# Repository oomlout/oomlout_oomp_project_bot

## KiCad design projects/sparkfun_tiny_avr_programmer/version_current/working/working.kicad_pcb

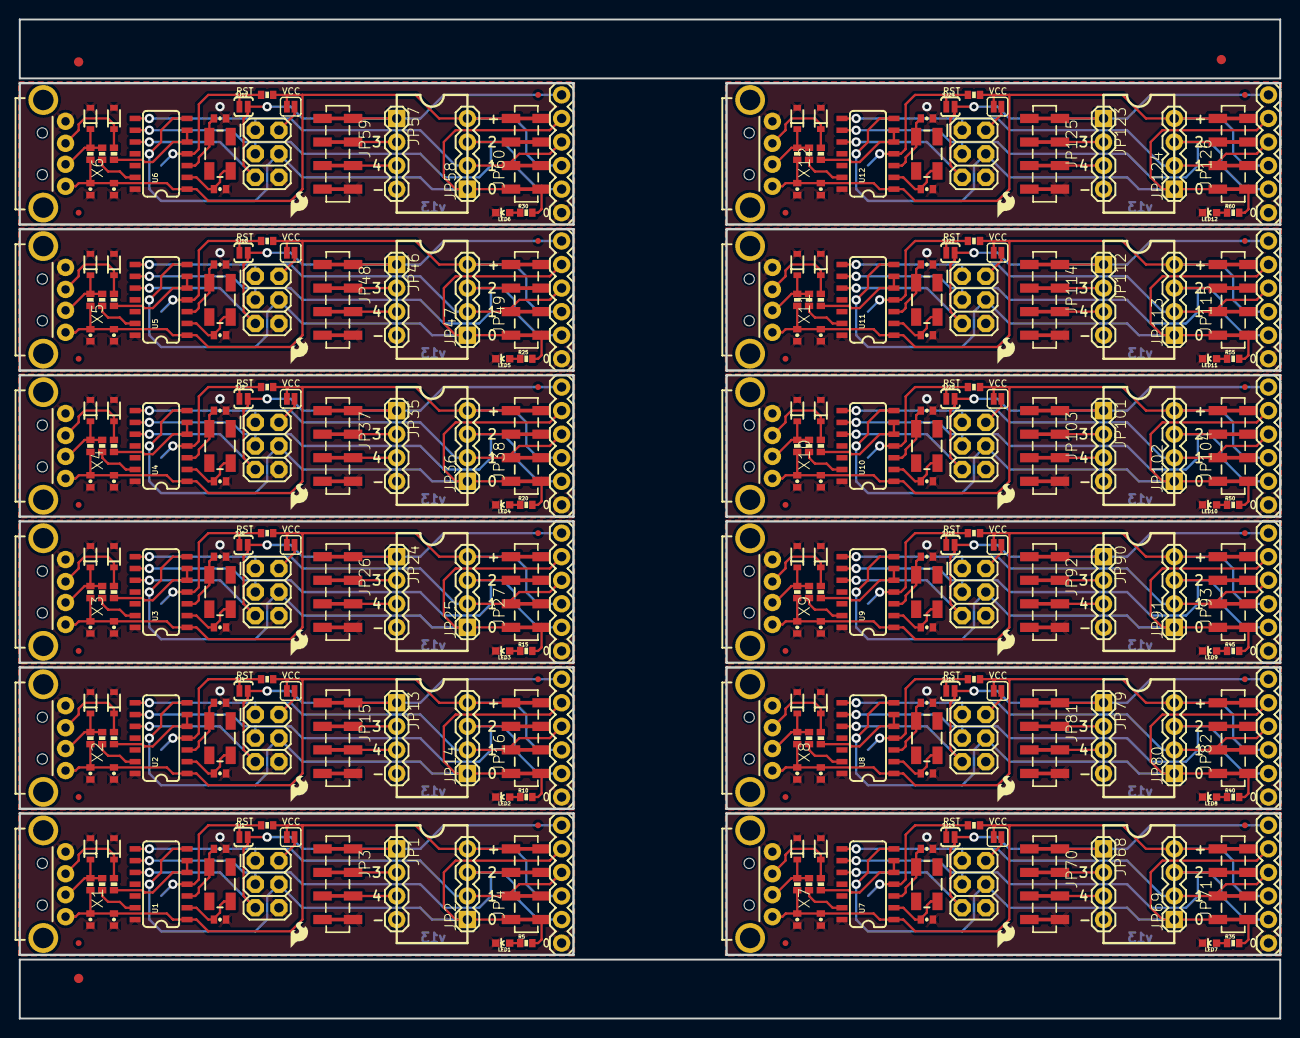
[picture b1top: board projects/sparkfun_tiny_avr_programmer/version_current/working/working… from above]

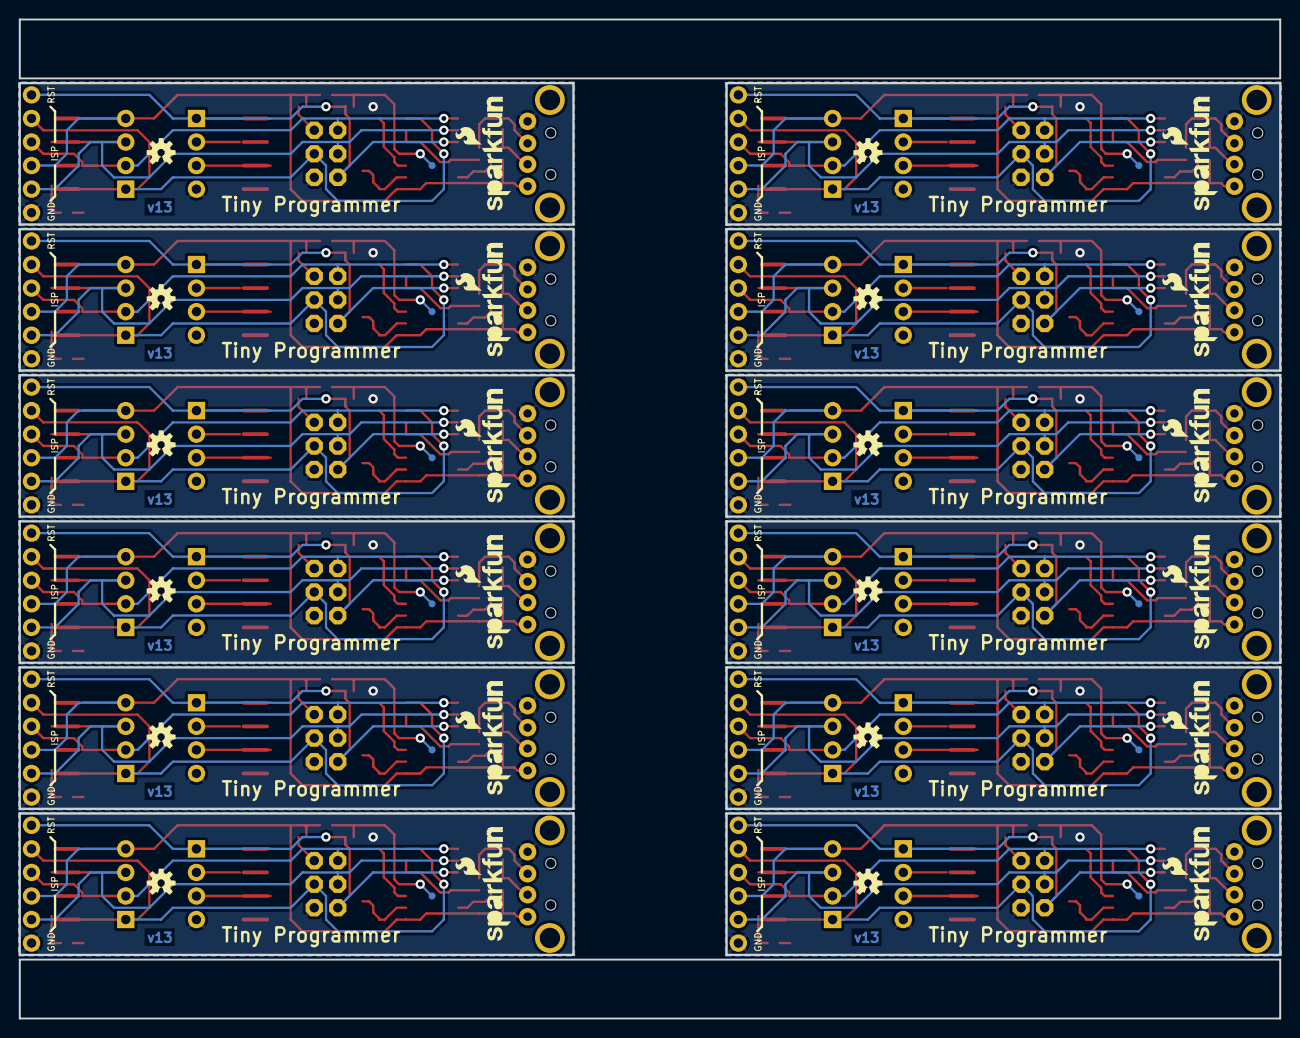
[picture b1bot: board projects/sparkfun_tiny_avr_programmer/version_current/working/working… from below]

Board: 2 copper layers, 135.9 x 107.7 mm, 363 parts (48 on the bottom side), 204 nets.

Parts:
C1, C5, C9, C13, C17, C21, C25, C29, C33, C37, C41, C45: 0.1uF; 0402-CAP
C2, C4, C7, C8, C11, C12, C15, C16, C19, C20, C23, C24, C27, C28, C31, C32, C35, C36, C39, C40, C43, C44, C47, C48: 18pF; 0402-CAP
C3, C6, C10, C14, C18, C22, C26, C30, C34, C38, C42, C46: 10uF; 0402-CAP
D1, D2, D3, D4, D5, D6, D7, D8, D9, D10, D11, D12, D13, D14, D15, D16, D17, D18, D19, D20, D21, D22, D23, D24: 3.3V; SOD-323
E$1, E$3, E$4: FIDUCIAL-1X2
JP1, JP2, JP13, JP14, JP24, JP25, JP35, JP36, JP46, JP47, JP57, JP58, JP68, JP69, JP79, JP80, JP90, JP91, JP101, JP102, JP112, JP113, JP123, JP124: 1X04
JP3, JP4, JP15, JP16, JP26, JP27, JP37, JP38, JP48, JP49, JP59, JP60, JP70, JP71, JP81, JP82, JP92, JP93, JP103, JP104, JP114, JP115, JP125, JP126: 1X04_SMD_STRAIGHT_COMBO
JP5, JP17, JP28, JP39, JP50, JP61, JP72, JP83, JP94, JP105, JP116, JP127: LOGO-SFENW2; SFE-NEW-WEB
JP6, JP11, JP18, JP21, JP29, JP32, JP40, JP43, JP51, JP54, JP62, JP65, JP73, JP76, JP84, JP87, JP95, JP98, JP106, JP109, JP117, JP120, JP128, JP131: LOGO-SFESK; SFE-LOGO-FLAME
JP7, JP8, JP19, JP20, JP30, JP31, JP41, JP42, JP52, JP53, JP63, JP64, JP74, JP75, JP85, JP86, JP96, JP97, JP107, JP108, JP118, JP119, JP129, JP130: FIDUCIALUFIDUCIAL; MICRO-FIDUCIAL
JP9, JP10, JP23, JP34, JP45, JP56, JP67, JP78, JP89, JP100, JP111, JP122: 2X3
JP12, JP22, JP33, JP44, JP55, JP66, JP77, JP88, JP99, JP110, JP121, JP132: 1X06
LED1, LED2, LED3, LED4, LED5, LED6, LED7, LED8, LED9, LED10, LED11, LED12: Yellow; LED-0603
Q1, Q2, Q3, Q4, Q5, Q6, Q7, Q8, Q9, Q10, Q11, Q12: 16MHz; CRYSTAL-SMD-5X3
R1, R2, R6, R7, R11, R12, R16, R17, R21, R22, R26, R27, R31, R32, R36, R37, R41, R42, R46, R47, R51, R52, R56, R57: 68; 0402-RES
R3, R8, R13, R18, R23, R28, R33, R38, R43, R48, R53, R58: 1.5K; 0402-RES
R4, R9, R14, R19, R24, R29, R34, R39, R44, R49, R54, R59: 10k; 0402-RES
R5, R10, R15, R20, R25, R30, R35, R40, R45, R50, R55, R60: 330; 0402-RES
SJ1, SJ4, SJ6, SJ8, SJ10, SJ12, SJ14, SJ16, SJ18, SJ20, SJ22, SJ24: SOLDERJUMPERNO; SJ_2S-NO
SJ2, SJ3, SJ5, SJ7, SJ9, SJ11, SJ13, SJ15, SJ17, SJ19, SJ21, SJ23: NC; SJ_2S
TP1, TP2, TP3, TP4, TP5, TP6, TP7, TP8, TP9, TP10, TP11, TP12: TEST-POINT3; PAD.03X.03
U1, U2, U3, U4, U5, U6, U7, U8, U9, U10, U11, U12: ATTINY84; SO14
U$1, U$2, U$3, U$4, U$5, U$6, U$7, U$8, U$9, U$10, U$11, U$12: OSHW-LOGOS; OSHW-LOGO-S
X1, X2, X3, X4, X5, X6, X7, X8, X9, X10, X11, X12: USB-A-H

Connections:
1: JP13.3, JP15.3
2: JP1.2, JP3.2
3: JP1.3, JP3.3
4: JP13.2, JP15.2
5: JP24.3, JP26.3
6: JP24.2, JP26.2
7: JP35.3, JP37.3
8: JP35.2, JP37.2
9: JP46.3, JP48.3
10: JP46.2, JP48.2
11: JP57.3, JP59.3
12: JP57.2, JP59.2
13: JP68.3, JP70.3
14: JP68.2, JP70.2
15: JP79.3, JP81.3
16: JP79.2, JP81.2
17: JP90.3, JP92.3
18: JP90.2, JP92.2
19: JP101.3, JP103.3
20: JP101.2, JP103.2
21: JP112.3, JP114.3
22: JP112.2, JP114.2
23: JP123.3, JP125.3
24: JP123.2, JP125.2
D+: R2.2, U1.5, U1.6
D+1: R7.2, U2.5, U2.6
D+2: R12.2, U3.5, U3.6
D+3: R17.2, U4.5, U4.6
D+4: R22.2, U5.5, U5.6
D+5: R27.2, U6.5, U6.6
D+6: R32.2, U7.5, U7.6
D+7: R37.2, U8.5, U8.6
D+8: R42.2, U9.5, U9.6
D+9: R47.2, U10.5, U10.6
D+10: R52.2, U11.5, U11.6
D+11: R57.2, U12.5, U12.6
D-: R1.2, U1.13
D-1: R6.2, U2.13
D-2: R11.2, U3.13
D-3: R16.2, U4.13
D-4: R21.2, U5.13
D-5: R26.2, U6.13
D-6: R31.2, U7.13
D-7: R36.2, U8.13
D-8: R41.2, U9.13
D-9: R46.2, U10.13
D-10: R51.2, U11.13
D-11: R56.2, U12.13
GND: C1.2, C2.2, C3.2, C4.2, D1.2, D2.2, JP1.4, JP3.4, JP9.6, JP12.6, LED1.C, U1.14, X1.GND
GND1: C5.2, C6.2, C7.2, C8.2, D3.2, D4.2, JP10.6, JP13.4, JP15.4, JP22.6, LED2.C, U2.14, X2.GND
GND2: C9.2, C10.2, C11.2, C12.2, D5.2, D6.2, JP23.6, JP24.4, JP26.4, JP33.6, LED3.C, U3.14, X3.GND
GND3: C13.2, C14.2, C15.2, C16.2, D7.2, D8.2, JP34.6, JP35.4, JP37.4, JP44.6, LED4.C, U4.14, X4.GND
GND4: C17.2, C18.2, C19.2, C20.2, D9.2, D10.2, JP45.6, JP46.4, JP48.4, JP55.6, LED5.C, U5.14, X5.GND
GND5: C21.2, C22.2, C23.2, C24.2, D11.2, D12.2, JP56.6, JP57.4, JP59.4, JP66.6, LED6.C, U6.14, X6.GND
GND6: C25.2, C26.2, C27.2, C28.2, D13.2, D14.2, JP67.6, JP68.4, JP70.4, JP77.6, LED7.C, U7.14, X7.GND
GND7: C29.2, C30.2, C31.2, C32.2, D15.2, D16.2, JP78.6, JP79.4, JP81.4, JP88.6, LED8.C, U8.14, X8.GND
GND8: C33.2, C34.2, C35.2, C36.2, D17.2, D18.2, JP89.6, JP90.4, JP92.4, JP99.6, LED9.C, U9.14, X9.GND
GND9: C37.2, C38.2, C39.2, C40.2, D19.2, D20.2, JP100.6, JP101.4, JP103.4, JP110.6, LED10.C, U10.14, X10.GND
GND10: C41.2, C42.2, C43.2, C44.2, D21.2, D22.2, JP111.6, JP112.4, JP114.4, JP121.6, LED11.C, U11.14, X11.GND
GND11: C45.2, C46.2, C47.2, C48.2, D23.2, D24.2, JP122.6, JP123.4, JP125.4, JP132.6, LED12.C, U12.14, X12.GND
MISO: JP2.2, JP4.2, JP9.1, JP12.3, U1.8
MISO1: JP10.1, JP14.2, JP16.2, JP22.3, U2.8
MISO2: JP23.1, JP25.2, JP27.2, JP33.3, U3.8
MISO3: JP34.1, JP36.2, JP38.2, JP44.3, U4.8
MISO4: JP45.1, JP47.2, JP49.2, JP55.3, U5.8
MISO5: JP56.1, JP58.2, JP60.2, JP66.3, U6.8
MISO6: JP67.1, JP69.2, JP71.2, JP77.3, U7.8
MISO7: JP78.1, JP80.2, JP82.2, JP88.3, U8.8
MISO8: JP89.1, JP91.2, JP93.2, JP99.3, U9.8
MISO9: JP100.1, JP102.2, JP104.2, JP110.3, U10.8
MISO10: JP111.1, JP113.2, JP115.2, JP121.3, U11.8
MISO11: JP122.1, JP124.2, JP126.2, JP132.3, U12.8
MOSI: JP2.1, JP4.1, JP9.4, JP12.2, R5.2, U1.7
MOSI1: JP10.4, JP14.1, JP16.1, JP22.2, R10.2, U2.7
MOSI2: JP23.4, JP25.1, JP27.1, JP33.2, R15.2, U3.7
MOSI3: JP34.4, JP36.1, JP38.1, JP44.2, R20.2, U4.7
MOSI4: JP45.4, JP47.1, JP49.1, JP55.2, R25.2, U5.7
MOSI5: JP56.4, JP58.1, JP60.1, JP66.2, R30.2, U6.7
MOSI6: JP67.4, JP69.1, JP71.1, JP77.2, R35.2, U7.7
MOSI7: JP78.4, JP80.1, JP82.1, JP88.2, R40.2, U8.7
MOSI8: JP89.4, JP91.1, JP93.1, JP99.2, R45.2, U9.7
MOSI9: JP100.4, JP102.1, JP104.1, JP110.2, R50.2, U10.7
MOSI10: JP111.4, JP113.1, JP115.1, JP121.2, R55.2, U11.7
MOSI11: JP122.4, JP124.1, JP126.1, JP132.2, R60.2, U12.7
unnamed: D2.1, R1.1, R3.1, X1.D-
unnamed: D1.1, R2.1, X1.D+
unnamed: C2.1, Q1.3, U1.3
unnamed: C4.1, Q1.1, U1.2
unnamed: LED1.A, R5.1
unnamed: D4.1, R6.1, R8.1, X2.D-
unnamed: D3.1, R7.1, X2.D+
unnamed: C7.1, Q2.3, U2.3
unnamed: C8.1, Q2.1, U2.2
unnamed: LED2.A, R10.1
unnamed: D6.1, R11.1, R13.1, X3.D-
unnamed: D5.1, R12.1, X3.D+
unnamed: C11.1, Q3.3, U3.3
unnamed: C12.1, Q3.1, U3.2
unnamed: LED3.A, R15.1
unnamed: D8.1, R16.1, R18.1, X4.D-
unnamed: D7.1, R17.1, X4.D+
unnamed: C15.1, Q4.3, U4.3
unnamed: C16.1, Q4.1, U4.2
unnamed: LED4.A, R20.1
unnamed: D10.1, R21.1, R23.1, X5.D-
unnamed: D9.1, R22.1, X5.D+
unnamed: C19.1, Q5.3, U5.3
unnamed: C20.1, Q5.1, U5.2
unnamed: LED5.A, R25.1
unnamed: D12.1, R26.1, R28.1, X6.D-
unnamed: D11.1, R27.1, X6.D+
unnamed: C23.1, Q6.3, U6.3
unnamed: C24.1, Q6.1, U6.2
unnamed: LED6.A, R30.1
unnamed: D14.1, R31.1, R33.1, X7.D-
unnamed: D13.1, R32.1, X7.D+
unnamed: C27.1, Q7.3, U7.3
unnamed: C28.1, Q7.1, U7.2
unnamed: LED7.A, R35.1
unnamed: D16.1, R36.1, R38.1, X8.D-
unnamed: D15.1, R37.1, X8.D+
unnamed: C31.1, Q8.3, U8.3
unnamed: C32.1, Q8.1, U8.2
unnamed: LED8.A, R40.1
unnamed: D18.1, R41.1, R43.1, X9.D-
unnamed: D17.1, R42.1, X9.D+
unnamed: C35.1, Q9.3, U9.3
unnamed: C36.1, Q9.1, U9.2
unnamed: LED9.A, R45.1
unnamed: D20.1, R46.1, R48.1, X10.D-
unnamed: D19.1, R47.1, X10.D+
unnamed: C39.1, Q10.3, U10.3
unnamed: C40.1, Q10.1, U10.2
unnamed: LED10.A, R50.1
unnamed: D22.1, R51.1, R53.1, X11.D-
unnamed: D21.1, R52.1, X11.D+
unnamed: C43.1, Q11.3, U11.3
unnamed: C44.1, Q11.1, U11.2
unnamed: LED11.A, R55.1
unnamed: D24.1, R56.1, R58.1, X12.D-
unnamed: D23.1, R57.1, X12.D+
unnamed: C47.1, Q12.3, U12.3
unnamed: C48.1, Q12.1, U12.2
unnamed: LED12.A, R60.1
RESET: R4.1, SJ1.1, TP1.P$1, U1.4
RESET1: R9.1, SJ4.1, TP2.P$1, U2.4
RESET2: R14.1, SJ6.1, TP3.P$1, U3.4
RESET3: R19.1, SJ8.1, TP4.P$1, U4.4
RESET4: R24.1, SJ10.1, TP5.P$1, U5.4
RESET5: R29.1, SJ12.1, TP6.P$1, U6.4
RESET6: R34.1, SJ14.1, TP7.P$1, U7.4
RESET7: R39.1, SJ16.1, TP8.P$1, U8.4
RESET8: R44.1, SJ18.1, TP9.P$1, U9.4
RESET9: R49.1, SJ20.1, TP10.P$1, U10.4
RESET10: R54.1, SJ22.1, TP11.P$1, U11.4
RESET11: R59.1, SJ24.1, TP12.P$1, U12.4
RST: JP1.1, JP3.1, JP9.5, JP12.1, SJ1.2, U1.10
RST1: JP10.5, JP13.1, JP15.1, JP22.1, SJ4.2, U2.10
RST2: JP23.5, JP24.1, JP26.1, JP33.1, SJ6.2, U3.10
RST3: JP34.5, JP35.1, JP37.1, JP44.1, SJ8.2, U4.10
RST4: JP45.5, JP46.1, JP48.1, JP55.1, SJ10.2, U5.10
RST5: JP56.5, JP57.1, JP59.1, JP66.1, SJ12.2, U6.10
RST6: JP67.5, JP68.1, JP70.1, JP77.1, SJ14.2, U7.10
RST7: JP78.5, JP79.1, JP81.1, JP88.1, SJ16.2, U8.10
RST8: JP89.5, JP90.1, JP92.1, JP99.1, SJ18.2, U9.10
RST9: JP100.5, JP101.1, JP103.1, JP110.1, SJ20.2, U10.10
RST10: JP111.5, JP112.1, JP114.1, JP121.1, SJ22.2, U11.10
RST11: JP122.5, JP123.1, JP125.1, JP132.1, SJ24.2, U12.10
SCK: JP2.3, JP4.3, JP9.3, JP12.5, U1.9
SCK1: JP10.3, JP14.3, JP16.3, JP22.5, U2.9
SCK2: JP23.3, JP25.3, JP27.3, JP33.5, U3.9
SCK3: JP34.3, JP36.3, JP38.3, JP44.5, U4.9
SCK4: JP45.3, JP47.3, JP49.3, JP55.5, U5.9
SCK5: JP56.3, JP58.3, JP60.3, JP66.5, U6.9
SCK6: JP67.3, JP69.3, JP71.3, JP77.5, U7.9
SCK7: JP78.3, JP80.3, JP82.3, JP88.5, U8.9
SCK8: JP89.3, JP91.3, JP93.3, JP99.5, U9.9
SCK9: JP100.3, JP102.3, JP104.3, JP110.5, U10.9
SCK10: JP111.3, JP113.3, JP115.3, JP121.5, U11.9
SCK11: JP122.3, JP124.3, JP126.3, JP132.5, U12.9
VCC: C1.1, C3.1, JP2.4, JP4.4, JP12.4, R3.2, R4.2, SJ2.1, U1.1, X1.VBUS
VCC1: C5.1, C6.1, JP14.4, JP16.4, JP22.4, R8.2, R9.2, SJ3.1, U2.1, X2.VBUS
VCC2: C9.1, C10.1, JP25.4, JP27.4, JP33.4, R13.2, R14.2, SJ5.1, U3.1, X3.VBUS
VCC3: C13.1, C14.1, JP36.4, JP38.4, JP44.4, R18.2, R19.2, SJ7.1, U4.1, X4.VBUS
VCC4: C17.1, C18.1, JP47.4, JP49.4, JP55.4, R23.2, R24.2, SJ9.1, U5.1, X5.VBUS
VCC5: C21.1, C22.1, JP58.4, JP60.4, JP66.4, R28.2, R29.2, SJ11.1, U6.1, X6.VBUS
VCC6: C25.1, C26.1, JP69.4, JP71.4, JP77.4, R33.2, R34.2, SJ13.1, U7.1, X7.VBUS
VCC7: C29.1, C30.1, JP80.4, JP82.4, JP88.4, R38.2, R39.2, SJ15.1, U8.1, X8.VBUS
VCC8: C33.1, C34.1, JP91.4, JP93.4, JP99.4, R43.2, R44.2, SJ17.1, U9.1, X9.VBUS
VCC9: C37.1, C38.1, JP102.4, JP104.4, JP110.4, R48.2, R49.2, SJ19.1, U10.1, X10.VBUS
VCC10: C41.1, C42.1, JP113.4, JP115.4, JP121.4, R53.2, R54.2, SJ21.1, U11.1, X11.VBUS
VCC11: C45.1, C46.1, JP124.4, JP126.4, JP132.4, R58.2, R59.2, SJ23.1, U12.1, X12.VBUS
VCC': JP9.2, SJ2.2
VCC'1: JP10.2, SJ3.2
VCC'2: JP23.2, SJ5.2
VCC'3: JP34.2, SJ7.2
VCC'4: JP45.2, SJ9.2
VCC'5: JP56.2, SJ11.2
VCC'6: JP67.2, SJ13.2
VCC'7: JP78.2, SJ15.2
VCC'8: JP89.2, SJ17.2
VCC'9: JP100.2, SJ19.2
VCC'10: JP111.2, SJ21.2
VCC'11: JP122.2, SJ23.2

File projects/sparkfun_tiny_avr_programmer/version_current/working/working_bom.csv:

"Id";"Designator";"Footprint";"Quantity";"Designation";"Supplier and ref";
1;"JP10,JP111,JP56,JP78,JP23,JP9,JP45,JP89,JP100,JP122,JP67,JP34";"2X3";12;"";;;
2;"JP80,JP47,JP69,JP13,JP35,JP25,JP102,JP57,JP124,JP14,JP2,JP58,JP1,JP113,JP36,JP123,JP101,JP90,JP112,JP79,JP24,JP68,JP46,JP91";"1X04";24;"";;;
3;"JP73,JP84,JP51,JP95,JP29,JP106,JP6,JP40,JP117,JP18,JP128,JP62,JP87,JP11,JP21,JP109,JP43,JP76,JP98,JP120,JP54,JP65,JP131,JP32";"SFE-LOGO-FLAME";24;"LOGO-SFESK";;;
4;"C4,C16,C31,C44,C8,C24,C2,C12,C20,C43,C27,C15,C19,C40,C48,C28,C39,C47,C11,C36,C7,C32,C23,C35";"0402-CAP";24;"18pF";;;
5;"SJ22,SJ6,SJ12,SJ4,SJ20,SJ1,SJ14,SJ16,SJ10,SJ8,SJ18,SJ24";"SJ_2S-NO";12;"SOLDERJUMPERNO";;;
6;"C6,C22,C3,C30,C14,C26,C46,C18,C10,C38,C34,C42";"0402-CAP";12;"10uF";;;
7;"R34,R19,R14,R59,R24,R4,R54,R49,R29,R44,R39,R9";"0402-RES";12;"10k";;;
8;"C37,C21,C13,C9,C45,C41,C25,C29,C17,C5,C33,C1";"0402-CAP";12;"0.1uF";;;
9;"D21,D14,D24,D23,D4,D1,D6,D12,D16,D3,D17,D9,D10,D18,D11,D22,D5,D7,D2,D13,D19,D15,D20,D8";"SOD-323";24;"3.3V";;;
10;"JP132,JP12,JP55,JP99,JP22,JP44,JP88,JP66,JP110,JP121,JP77,JP33";"1X06";12;"";;;
11;"R27,R1,R26,R57,R56,R11,R2,R47,R12,R17,R6,R21,R7,R36,R31,R37,R22,R42,R32,R46,R41,R51,R52,R16";"0402-RES";24;"68";;;
12;"JP20,JP107,JP64,JP63,JP41,JP8,JP53,JP129,JP42,JP30,JP52,JP86,JP7,JP130,JP118,JP74,JP75,JP108,JP96,JP119,JP31,JP97,JP19,JP85";"MICRO-FIDUCIAL";24;"FIDUCIALUFIDUCIAL";;;
13;"X8,X5,X3,X6,X1,X11,X4,X2,X10,X9,X7,X12";"USB-A-H";12;"USB-A-H";;;
14;"E$1,E$4,E$3";"FIDUCIAL-1X2";3;"";;;
15;"SJ9,SJ7,SJ11,SJ21,SJ17,SJ13,SJ23,SJ2,SJ5,SJ3,SJ19,SJ15";"SJ_2S";12;"NC";;;
16;"JP81,JP15,JP104,JP3,JP125,JP38,JP82,JP4,JP37,JP49,JP27,JP114,JP26,JP48,JP70,JP103,JP16,JP126,JP92,JP60,JP115,JP71,JP93,JP59";"1X04_SMD_STRAIGHT_COMBO";24;"";;;
17;"R53,R58,R33,R3,R43,R48,R8,R13,R18,R23,R38,R28";"0402-RES";12;"1.5K";;;
18;"R45,R40,R50,R60,R15,R20,R10,R30,R35,R25,R55,R5";"0402-RES";12;"330";;;
19;"Q1,Q12,Q10,Q11,Q6,Q7,Q2,Q3,Q9,Q4,Q5,Q8";"CRYSTAL-SMD-5X3";12;"16MHz";;;
20;"LED7,LED5,LED4,LED1,LED8,LED6,LED11,LED10,LED2,LED12,LED9,LED3";"LED-0603";12;"Yellow";;;
21;"U3,U12,U9,U5,U10,U6,U7,U4,U1,U8,U2,U11";"SO14";12;"ATTINY84";;;
22;"JP50,JP39,JP17,JP127,JP72,JP116,JP28,JP61,JP94,JP5,JP105,JP83";"SFE-NEW-WEB";12;"LOGO-SFENW2";;;
23;"TP5,TP3,TP1,TP9,TP10,TP12,TP11,TP7,TP6,TP8,TP4,TP2";"PAD.03X.03";12;"TEST-POINT3";;;
24;"U$11,U$12,U$8,U$3,U$2,U$7,U$1,U$9,U$10,U$6,U$5,U$4";"OSHW-LOGO-S";12;"OSHW-LOGOS";;;

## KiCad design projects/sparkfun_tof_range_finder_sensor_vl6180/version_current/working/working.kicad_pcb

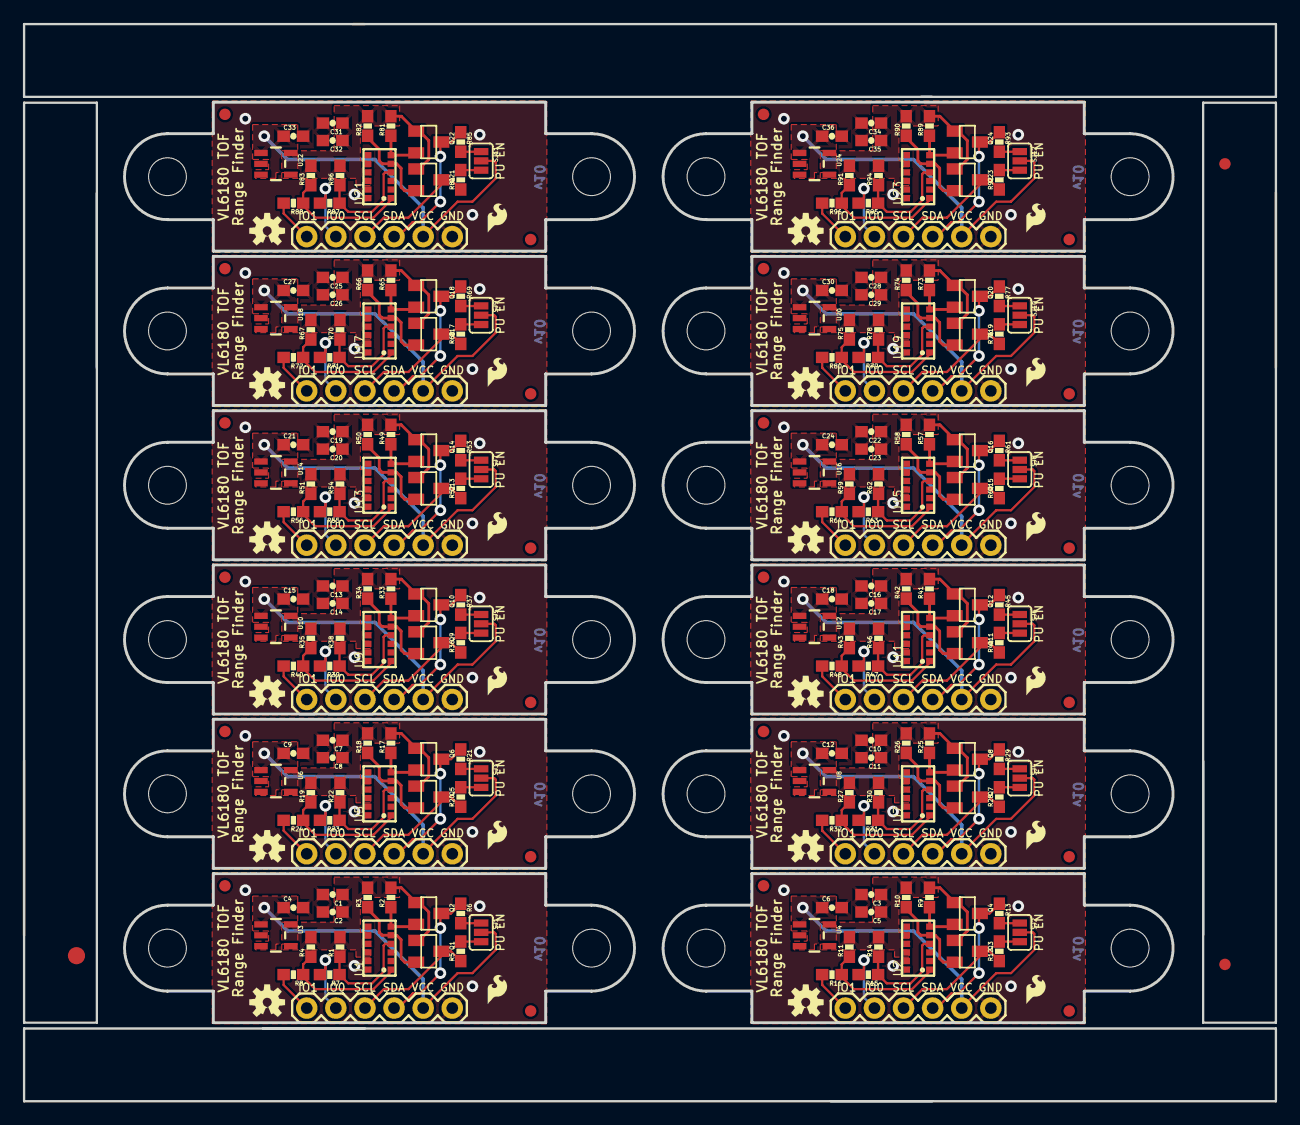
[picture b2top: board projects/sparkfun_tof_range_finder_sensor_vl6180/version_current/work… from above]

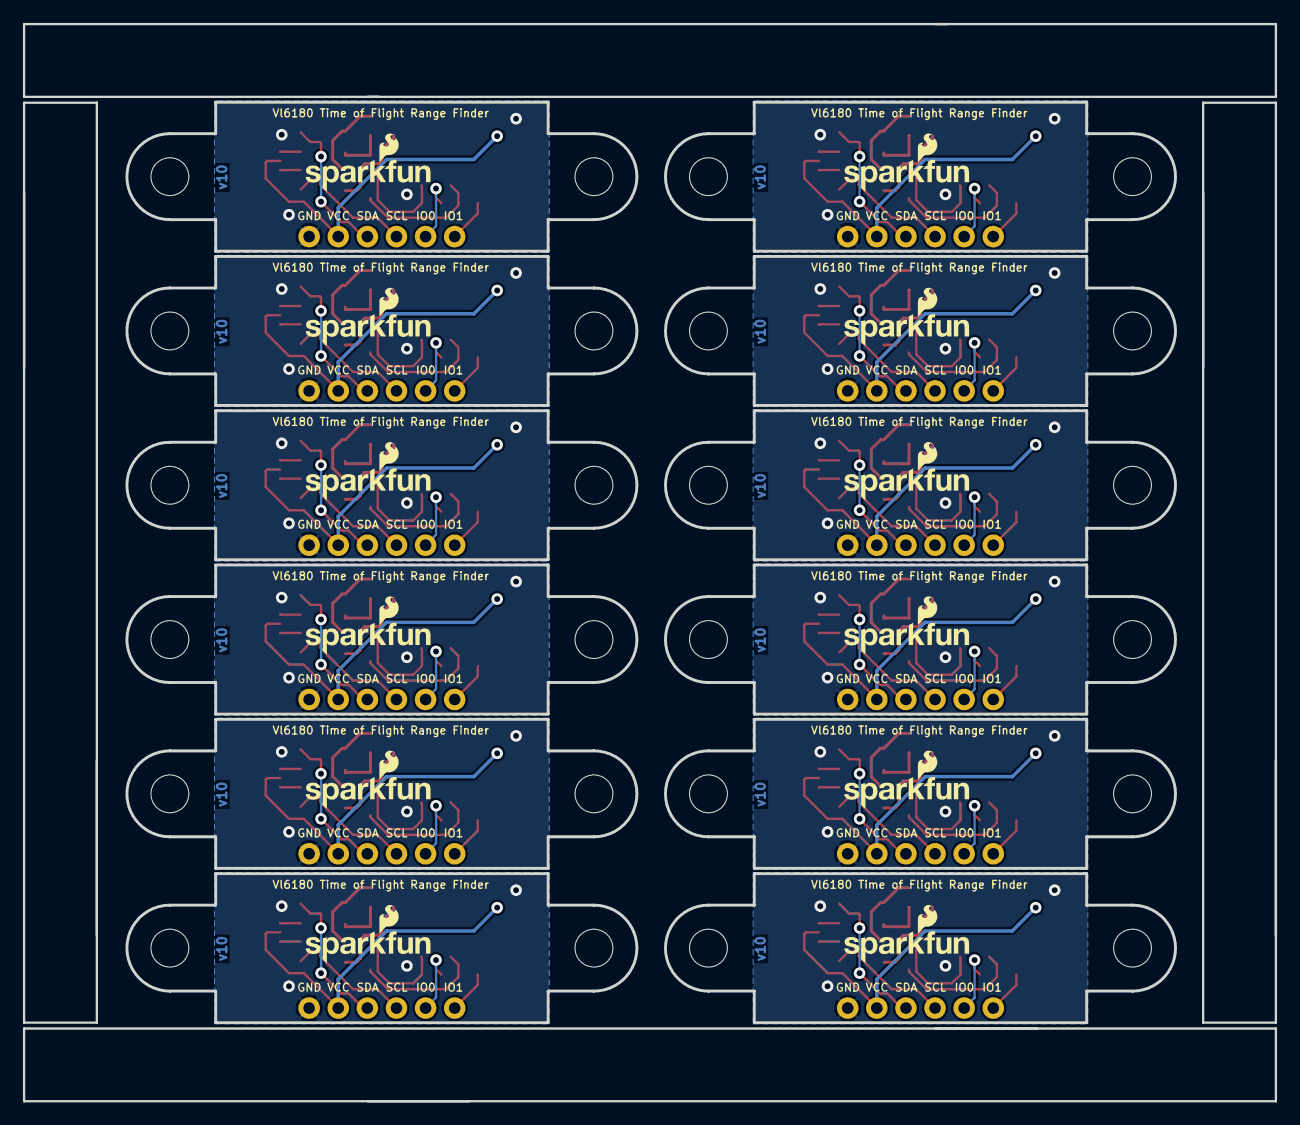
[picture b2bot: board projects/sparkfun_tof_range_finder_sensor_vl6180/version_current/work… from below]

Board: 2 copper layers, 109.2 x 94.0 mm, 291 parts (12 on the bottom side), 156 nets.

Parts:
C1, C3, C7, C10, C13, C16, C19, C22, C25, C28, C31, C34: 4.7uF; 0603-CAP
C2, C4, C5, C6, C8, C9, C11, C12, C14, C15, C17, C18, C20, C21, C23, C24, C26, C27, C29, C30, C32, C33, C35, C36: 0.1uF; 0603-CAP
E$1: FIDUCIAL-1.5X3
E$4, E$5: FIDUCIAL-1X2
FID1, FID2, FID3, FID4, FID5, FID6, FID7, FID8, FID9, FID10, FID11, FID12, FID13, FID14, FID15, FID16, FID17, FID18, FID19, FID20, FID21, FID22, FID23, FID24: FIDUCIAL1X2; FIDUCIAL-1X2
JP1, JP2, JP3, JP4, JP5, JP6, JP7, JP8, JP9, JP10, JP11, JP12: 1X06
LOGO1, LOGO3, LOGO5, LOGO7, LOGO9, LOGO11, LOGO13, LOGO15, LOGO17, LOGO19, LOGO21, LOGO23: SFE_LOGO_NAME_FLAME.1_INCH; SFE_LOGO_NAME_FLAME_.1
LOGO2, LOGO4, LOGO6, LOGO8, LOGO10, LOGO12, LOGO14, LOGO16, LOGO18, LOGO20, LOGO22, LOGO24: OSHW-LOGOS; OSHW-LOGO-S
Q1, Q2, Q3, Q4, Q5, Q6, Q7, Q8, Q9, Q10, Q11, Q12, Q13, Q14, Q15, Q16, Q17, Q18, Q19, Q20, Q21, Q22, Q23, Q24: BSS138; SOT23
R1, R4, R11, R14, R19, R22, R27, R30, R35, R38, R43, R46, R51, R54, R59, R62, R67, R70, R75, R78, R83, R86, R91, R94: 47k; 0603-RES
R2, R3, R5, R6, R9, R10, R12, R13, R17, R18, R20, R21, R25, R26, R28, R29, R33, R34, R36, R37, R41, R42, R44, R45, R49, R50, R52, R53, R57, R58, R60, R61, R65, R66, R68, R69, R73, R74, R76, R77, R81, R82, R84, R85, R89, R90, R92, R93: 2.2k; 0603-RES
R7, R8, R15, R16, R23, R24, R31, R32, R39, R40, R47, R48, R55, R56, R63, R64, R71, R72, R79, R80, R87, R88, R95, R96: 10k; 0603-RES
SJ1, SJ2, SJ3, SJ4, SJ5, SJ6, SJ7, SJ8, SJ9, SJ10, SJ11, SJ12: PAD-JUMPER-3-NC_BY_PASTE_YES_SILK_FULL_BOX
STANDOFF1, STANDOFF2, STANDOFF3, STANDOFF4, STANDOFF5, STANDOFF6, STANDOFF7, STANDOFF8, STANDOFF9, STANDOFF10, STANDOFF11, STANDOFF12, STANDOFF13, STANDOFF14, STANDOFF15, STANDOFF16, STANDOFF17, STANDOFF18, STANDOFF19, STANDOFF20, STANDOFF21, STANDOFF22, STANDOFF23, STANDOFF24: STAND-OFF
U1, U2, U5, U7, U9, U11, U13, U15, U17, U19, U21, U23: VL6180
U3, U4, U6, U8, U10, U12, U14, U16, U18, U20, U22, U24: MIC5219 3.3V; SOT23-5
U$1, U$2, U$3, U$4, U$5, U$6, U$7, U$8, U$9, U$10, U$11, U$12: SFE_LOGO_FLAME_.1

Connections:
2.8V: C1.1, C2.1, Q1.1, Q2.1, R1.2, R2.2, R3.2, R4.2, U1.8, U1.10, U3.5
2.8V1: C3.1, C5.1, Q3.1, Q4.1, R9.2, R10.2, R11.2, R14.2, U2.8, U2.10, U4.5
2.8V2: C7.1, C8.1, Q5.1, Q6.1, R17.2, R18.2, R19.2, R22.2, U5.8, U5.10, U6.5
2.8V3: C10.1, C11.1, Q7.1, Q8.1, R25.2, R26.2, R27.2, R30.2, U7.8, U7.10, U8.5
2.8V4: C13.1, C14.1, Q9.1, Q10.1, R33.2, R34.2, R35.2, R38.2, U9.8, U9.10, U10.5
2.8V5: C16.1, C17.1, Q11.1, Q12.1, R41.2, R42.2, R43.2, R46.2, U11.8, U11.10, U12.5
2.8V6: C19.1, C20.1, Q13.1, Q14.1, R49.2, R50.2, R51.2, R54.2, U13.8, U13.10, U14.5
2.8V7: C22.1, C23.1, Q15.1, Q16.1, R57.2, R58.2, R59.2, R62.2, U15.8, U15.10, U16.5
2.8V8: C25.1, C26.1, Q17.1, Q18.1, R65.2, R66.2, R67.2, R70.2, U17.8, U17.10, U18.5
2.8V9: C28.1, C29.1, Q19.1, Q20.1, R73.2, R74.2, R75.2, R78.2, U19.8, U19.10, U20.5
2.8V10: C31.1, C32.1, Q21.1, Q22.1, R81.2, R82.2, R83.2, R86.2, U21.8, U21.10, U22.5
2.8V11: C34.1, C35.1, Q23.1, Q24.1, R89.2, R90.2, R91.2, R94.2, U23.8, U23.10, U24.5
GND: C1.2, C2.2, C4.2, JP1.1, U1.9, U1.12, U3.2
GND1: C3.2, C5.2, C6.2, JP2.1, U2.9, U2.12, U4.2
GND2: C7.2, C8.2, C9.2, JP3.1, U5.9, U5.12, U6.2
GND3: C10.2, C11.2, C12.2, JP4.1, U7.9, U7.12, U8.2
GND4: C13.2, C14.2, C15.2, JP5.1, U9.9, U9.12, U10.2
GND5: C16.2, C17.2, C18.2, JP6.1, U11.9, U11.12, U12.2
GND6: C19.2, C20.2, C21.2, JP7.1, U13.9, U13.12, U14.2
GND7: C22.2, C23.2, C24.2, JP8.1, U15.9, U15.12, U16.2
GND8: C25.2, C26.2, C27.2, JP9.1, U17.9, U17.12, U18.2
GND9: C28.2, C29.2, C30.2, JP10.1, U19.9, U19.12, U20.2
GND10: C31.2, C32.2, C33.2, JP11.1, U21.9, U21.12, U22.2
GND11: C34.2, C35.2, C36.2, JP12.1, U23.9, U23.12, U24.2
GPIO0: JP1.5, R7.2
GPIO1: JP1.6, R8.2
GPIO2: JP2.5, R15.2
GPIO3: JP2.6, R16.2
GPIO4: JP3.5, R23.2
GPIO5: JP3.6, R24.2
GPIO6: JP4.5, R31.2
GPIO7: JP4.6, R32.2
GPIO8: JP5.5, R39.2
GPIO9: JP5.6, R40.2
GPIO10: JP6.5, R47.2
GPIO11: JP6.6, R48.2
GPIO12: JP7.5, R55.2
GPIO13: JP7.6, R56.2
GPIO14: JP8.5, R63.2
GPIO15: JP8.6, R64.2
GPIO16: JP9.5, R71.2
GPIO17: JP9.6, R72.2
GPIO18: JP10.5, R79.2
GPIO19: JP10.6, R80.2
GPIO20: JP11.5, R87.2
GPIO21: JP11.6, R88.2
GPIO22: JP12.5, R95.2
GPIO23: JP12.6, R96.2
unnamed: R13.2, SJ2.1
unnamed: R6.2, SJ1.1
unnamed: R5.2, SJ1.3
unnamed: R12.2, SJ2.3
unnamed: R14.1, R15.1, U2.4
unnamed: R11.1, R16.1, U2.1
unnamed: R21.2, SJ3.1
unnamed: R20.2, SJ3.3
unnamed: R22.1, R23.1, U5.4
unnamed: R19.1, R24.1, U5.1
unnamed: R29.2, SJ4.1
unnamed: R28.2, SJ4.3
unnamed: R30.1, R31.1, U7.4
unnamed: R27.1, R32.1, U7.1
unnamed: R37.2, SJ5.1
unnamed: R36.2, SJ5.3
unnamed: R38.1, R39.1, U9.4
unnamed: R35.1, R40.1, U9.1
unnamed: R45.2, SJ6.1
unnamed: R44.2, SJ6.3
unnamed: R46.1, R47.1, U11.4
unnamed: R43.1, R48.1, U11.1
unnamed: R53.2, SJ7.1
unnamed: R52.2, SJ7.3
unnamed: R54.1, R55.1, U13.4
unnamed: R51.1, R56.1, U13.1
unnamed: R61.2, SJ8.1
unnamed: R60.2, SJ8.3
unnamed: R62.1, R63.1, U15.4
unnamed: R59.1, R64.1, U15.1
unnamed: R69.2, SJ9.1
unnamed: R68.2, SJ9.3
unnamed: R70.1, R71.1, U17.4
unnamed: R67.1, R72.1, U17.1
unnamed: R77.2, SJ10.1
unnamed: R76.2, SJ10.3
unnamed: R78.1, R79.1, U19.4
unnamed: R75.1, R80.1, U19.1
unnamed: R85.2, SJ11.1
unnamed: R84.2, SJ11.3
unnamed: R86.1, R87.1, U21.4
unnamed: R83.1, R88.1, U21.1
unnamed: R93.2, SJ12.1
unnamed: R92.2, SJ12.3
unnamed: R94.1, R95.1, U23.4
unnamed: R91.1, R96.1, U23.1
unnamed: R1.1, R7.1, U1.4
unnamed: R4.1, R8.1, U1.1
SCL: JP1.4, Q1.3, R5.1
SCL1: JP2.4, Q3.3, R12.1
SCL2: JP3.4, Q5.3, R20.1
SCL3: JP4.4, Q7.3, R28.1
SCL4: JP5.4, Q9.3, R36.1
SCL5: JP6.4, Q11.3, R44.1
SCL6: JP7.4, Q13.3, R52.1
SCL7: JP8.4, Q15.3, R60.1
SCL8: JP9.4, Q17.3, R68.1
SCL9: JP10.4, Q19.3, R76.1
SCL10: JP11.4, Q21.3, R84.1
SCL11: JP12.4, Q23.3, R92.1
SCL_LV: Q1.2, R3.1, U1.5
SCL_LV1: Q3.2, R10.1, U2.5
SCL_LV2: Q5.2, R18.1, U5.5
SCL_LV3: Q7.2, R26.1, U7.5
SCL_LV4: Q9.2, R34.1, U9.5
SCL_LV5: Q11.2, R42.1, U11.5
SCL_LV6: Q13.2, R50.1, U13.5
SCL_LV7: Q15.2, R58.1, U15.5
SCL_LV8: Q17.2, R66.1, U17.5
SCL_LV9: Q19.2, R74.1, U19.5
SCL_LV10: Q21.2, R82.1, U21.5
SCL_LV11: Q23.2, R90.1, U23.5
SDA: JP1.3, Q2.3, R6.1
SDA1: JP2.3, Q4.3, R13.1
SDA2: JP3.3, Q6.3, R21.1
SDA3: JP4.3, Q8.3, R29.1
SDA4: JP5.3, Q10.3, R37.1
SDA5: JP6.3, Q12.3, R45.1
SDA6: JP7.3, Q14.3, R53.1
SDA7: JP8.3, Q16.3, R61.1
SDA8: JP9.3, Q18.3, R69.1
SDA9: JP10.3, Q20.3, R77.1
SDA10: JP11.3, Q22.3, R85.1
SDA11: JP12.3, Q24.3, R93.1
SDA_LV: Q2.2, R2.1, U1.6
SDA_LV1: Q4.2, R9.1, U2.6
SDA_LV2: Q6.2, R17.1, U5.6
SDA_LV3: Q8.2, R25.1, U7.6
SDA_LV4: Q10.2, R33.1, U9.6
SDA_LV5: Q12.2, R41.1, U11.6
SDA_LV6: Q14.2, R49.1, U13.6
SDA_LV7: Q16.2, R57.1, U15.6
SDA_LV8: Q18.2, R65.1, U17.6
SDA_LV9: Q20.2, R73.1, U19.6
SDA_LV10: Q22.2, R81.1, U21.6
SDA_LV11: Q24.2, R89.1, U23.6
VCC: C4.1, JP1.2, SJ1.2, U3.1, U3.3
VCC1: C6.1, JP2.2, SJ2.2, U4.1, U4.3
VCC2: C9.1, JP3.2, SJ3.2, U6.1, U6.3
VCC3: C12.1, JP4.2, SJ4.2, U8.1, U8.3
VCC4: C15.1, JP5.2, SJ5.2, U10.1, U10.3
VCC5: C18.1, JP6.2, SJ6.2, U12.1, U12.3
VCC6: C21.1, JP7.2, SJ7.2, U14.1, U14.3
VCC7: C24.1, JP8.2, SJ8.2, U16.1, U16.3
VCC8: C27.1, JP9.2, SJ9.2, U18.1, U18.3
VCC9: C30.1, JP10.2, SJ10.2, U20.1, U20.3
VCC10: C33.1, JP11.2, SJ11.2, U22.1, U22.3
VCC11: C36.1, JP12.2, SJ12.2, U24.1, U24.3

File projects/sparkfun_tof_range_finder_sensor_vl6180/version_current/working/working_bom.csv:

"Id";"Designator";"Footprint";"Quantity";"Designation";"Supplier and ref";
1;"LOGO2,LOGO24,LOGO18,LOGO10,LOGO4,LOGO22,LOGO8,LOGO12,LOGO14,LOGO6,LOGO20,LOGO16";"OSHW-LOGO-S";12;"OSHW-LOGOS";;;
2;"Q2,Q17,Q21,Q16,Q14,Q4,Q15,Q8,Q19,Q6,Q20,Q7,Q9,Q18,Q1,Q23,Q12,Q3,Q24,Q11,Q13,Q22,Q10,Q5";"SOT23";24;"BSS138";;;
3;"R69,R50,R5,R89,R45,R25,R12,R66,R76,R26,R53,R57,R37,R77,R36,R3,R61,R9,R81,R60,R42,R68,R28,R17,R34,R85,R2,R13,R10,R52,R41,R33,R20,R93,R84,R21,R29,R58,R90,R49,R6,R82,R73,R44,R74,R92,R18,R65";"0603-RES";48;"2.2k";;;
4;"R55,R95,R64,R47,R24,R56,R88,R71,R72,R31,R32,R96,R15,R48,R8,R16,R87,R23,R7,R39,R79,R63,R80,R40";"0603-RES";24;"10k";;;
5;"STANDOFF21,STANDOFF2,STANDOFF17,STANDOFF14,STANDOFF22,STANDOFF11,STANDOFF24,STANDOFF8,STANDOFF9,STANDOFF4,STANDOFF12,STANDOFF10,STANDOFF13,STANDOFF18,STANDOFF6,STANDOFF23,STANDOFF3,STANDOFF20,STANDOFF5,STANDOFF19,STANDOFF15,STANDOFF1,STANDOFF7,STANDOFF16";"STAND-OFF";24;"STAND-OFF";;;
6;"FID20,FID14,FID15,FID22,FID23,FID18,FID21,FID1,FID17,FID3,FID12,FID13,FID10,FID19,FID8,FID2,FID16,FID6,FID24,FID7,FID5,FID9,FID4,FID11";"FIDUCIAL-1X2";24;"FIDUCIAL1X2";;;
7;"C1,C19,C7,C28,C16,C13,C10,C3,C25,C31,C34,C22";"0603-CAP";12;"4.7uF";;;
8;"R46,R27,R62,R11,R70,R91,R94,R75,R54,R1,R67,R83,R43,R78,R38,R59,R19,R35,R30,R14,R4,R51,R22,R86";"0603-RES";24;"47k";;;
9;"U18,U3,U14,U12,U4,U8,U20,U16,U22,U24,U6,U10";"SOT23-5";12;"MIC5219 3.3V";;;
10;"U$6,U$4,U$3,U$7,U$8,U$12,U$5,U$10,U$11,U$9,U$1,U$2";"SFE_LOGO_FLAME_.1";12;"";;;
11;"JP10,JP4,JP1,JP3,JP11,JP7,JP5,JP9,JP12,JP8,JP6,JP2";"1X06";12;"";;;
12;"E$4,E$5";"FIDUCIAL-1X2";2;"";;;
13;"SJ6,SJ8,SJ3,SJ4,SJ10,SJ1,SJ9,SJ12,SJ11,SJ7,SJ2,SJ5";"PAD-JUMPER-3-NC_BY_PASTE_YES_SILK_FULL_BOX";12;"";;;
14;"U1,U7,U5,U9,U21,U17,U11,U15,U19,U23,U13,U2";"VL6180";12;"VL6180";;;
15;"C21,C17,C35,C26,C33,C18,C14,C15,C8,C2,C6,C32,C36,C24,C11,C30,C20,C29,C23,C4,C27,C5,C12,C9";"0603-CAP";24;"0.1uF";;;
16;"E$1";"FIDUCIAL-1.5X3";1;"";;;
17;"LOGO9,LOGO13,LOGO19,LOGO17,LOGO1,LOGO5,LOGO23,LOGO7,LOGO11,LOGO3,LOGO15,LOGO21";"SFE_LOGO_NAME_FLAME_.1";12;"SFE_LOGO_NAME_FLAME.1_INCH";;;

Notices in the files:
projects/sparkfun_tiny_avr_programmer/version_current/working/working.kicad_sch:
http://creativecommons.org/licenses/by-sa/3.0
Released under the Creative Commons
projects/sparkfun_tof_range_finder_sensor_vl6180/version_current/working/working.kicad_sch:
https://creativecommons.org/licenses/by-sa/4.0
projects/sparkfun_tri_color_breakout/version_current/working/working.kicad_sch:
Released under the Creative Commons Attribution Share-Alike 3.0 License
parts and their libraries:
Released under the Creative Commons Attribution Share-Alike 4.0 License
